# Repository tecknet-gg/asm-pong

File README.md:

<div align="center">

  <h1>asm-pong</h1>

  <p>pong implemented in assembly!</p>

</div>

## What!?

Basically what the subheading said! The classic game of pong implemented in assembly, running on a PIC16F18346 based console(-ish).

The PIC16F18346 console boasts a whopping 2KB of RAM, and a massive 28KB of flash memory, clocked at a blazing 32MHz! The game is displayed on a 128x64px OLED screen, with the player paddles being controlled by two potentiometers. Scores are displayed on two dedicated seven segment displays, with the sound effects being generated by a singular active buzzer. The console uses 3.3V, supplied by a regulated (up to 6V) power supply. Also features a dedicated ICSP header for easy programming using a PICkit3 or similar. 

## Hardware Overview
- PIC16F18346: Enhanced 8 bit, 20 pin mid-range PIC
- SSD1306: 128x64 pixel SPI OLED screen
- Alps RK09: Input potentiometers
- MCP1700-3302E: 3.3V regulated input
- 74HC595N: Daisy chained shift registers
- LD3161-AS: 0.36" red seven segment displays

## BOM

The detailed bill of materials file can be found under [pcb/production/bom.csv](pcb/production/bom.csv). All the components were sourced from AliExpress besides the PIC, since LCSC has much better pricing for the same. The table is reproduced below for convenience.

>[!Note]
> The capacitor and resistor pricing is the entire bundle price, including all the required values for this project.

| Item                       | Quantity | Description              |  Price | Source                                                                                                                                                                                                  |
| -------------------------- | -------: | ------------------------ | -----: | ------------------------------------------------------------------------------------------------------------------------------------------------------------------------------------------------------- |
| PIC16F18346-I/P            |        1 | Microcontroller          |  £1.81 | [LCSC](https://www.lcsc.com/product-detail/C647086.html?s_z=n_q_pic16f18346&spm=wm.fly.bg.0.xh&lcsc_vid=RFZZAwJQR1YIUFFXEgMNVgdQQAUIAQEER1IKUlZfRlcxVlNeQFhfXlBeRFFcVTsOAxUeFF5JWBYZEEoKFBINSQcJGk4%3D) |
| 100nF Ceramic Capacitor    |        7 | Decoupling capacitor     |      £1.93 | [AliExpress](https://www.aliexpress.com/item/1005008244407175.html?spm=a2g0o.order_list.order_list_main.203.33291802JVuyPM)                                                                             |
| 1µF Electrolytic Capacitor |        2 | Bulk capacitor           |      £1.96 | [AliExpress](https://www.aliexpress.com/item/1005006244064108.html?spm=a2g0o.order_list.order_list_main.316.33291802JVuyPM)                                                                             |
| SSD1306                    |        1 | OLED screen              |  £2.33 | [AliExpress](https://www.aliexpress.com/item/1005006379964006.html?spm=a2g0o.order_list.order_list_main.180.33291802JVuyPM)                                                                             |
| SN74HC595                  |        2 | Shift registers          |  £0.80 | [AliExpress](https://www.aliexpress.com/item/32796581727.html?spm=a2g0o.order_list.order_list_main.163.33291802JVuyPM)                                                                                  |
| LD-3161-AS                 |        2 | Seven-segment display    |  £2.33 | [AliExpress](https://www.aliexpress.com/item/1005007531476613.html?spm=a2g0o.order_list.order_list_main.158.33291802JVuyPM)                                                                             |
| Tactile Buttons            |        2 | Push buttons             |  £1.16 | [AliExpress](https://www.aliexpress.com/item/1005010485096642.html?spm=a2g0o.order_list.order_list_main.138.33291802JVuyPM)                                                                             |
| RV09 Potentiometers        |        2 | Potentiometers           |  £1.08 | [AliExpress](https://www.aliexpress.com/item/4000665266312.html?spm=a2g0o.order_list.order_list_main.128.33291802JVuyPM)                                                                                |
| Buzzer                     |        1 | Active buzzer            |  £1.80 | [AliExpress](https://www.aliexpress.com/item/1005010321957502.html?spm=a2g0o.order_list.order_list_main.80.33291802JVuyPM)                                                                              |
| 2N2222 NPN                 |        1 | Buzzer transistor        |  £1.00 | [AliExpress](https://www.aliexpress.com/item/1005005776372882.html?spm=a2g0o.order_list.order_list_main.68.33291802JVuyPM)                                                                              |
| 1N4148 Diode               |        1 | Flyback diode            |  £1.00 | [AliExpress](https://www.aliexpress.com/item/1005008512103805.html?spm=a2g0o.order_list.order_list_main.50.33291802JVuyPM)                                                                              |
| Knurled Metal Tone Knob    |        2 | Potentiometer knob       |  £2.01 | [AliExpress](https://www.aliexpress.com/item/1005002748625431.html?spm=a2g0o.order_list.order_list_main.35.33291802JVuyPM)                                                                              |
| MCP1700-3302E/TO           |        1 | 3.3V LDO                 |  £2.39 | [AliExpress](https://www.aliexpress.com/item/1005012279859529.html?spm=a2g0o.order_list.order_list_main.17.33291802JVuyPM)                                                                              |
| DC Power Barrel            |        1 | VIN input                |  £1.00 | [AliExpress](https://www.aliexpress.com/item/1005003329078538.html)                                                                                                                                     |
| 220Ω THT Resistor          |       16 | Current limiting         | £2.69|[AliExpress](https://www.aliexpress.com/item/1005007714306585.html?spm=a2g0o.order_list.order_list_main.98.74b31802kVDw05)                                                                                                                                                                                                       |
| 10kΩ THT Resistor          |        3 | RC/MCLR pull-up          |      £2.69|[AliExpress](https://www.aliexpress.com/item/1005007714306585.html?spm=a2g0o.order_list.order_list_main.98.74b31802kVDw05)                                                                                                                                                                                                     |
| 1kΩ THT Resistor           |        1 | Transistor base resistor |    £2.69  | [AliExpress](https://www.aliexpress.com/item/1005007714306585.html?spm=a2g0o.order_list.order_list_main.98.74b31802kVDw05)                                                                                                                                                                                                       |
| PICkit 3                   |        1 | ICSP programmer          | £14.19 | [AliExpress](https://www.aliexpress.com/item/1005007470418989.html?spm=a2g0o.order_list.order_list_main.168.33291802JVuyPM)                                                                             |
| PCB                        |        5 | Custom PCB               |     ~   | [pcb/production](pcb/production)                                                                           |

## Schematic

## PCB

## Assembly

PCB production files can be found under [pcb/production](pcb/production). Board is under 100x100mm, so should cost less than $5 for five boards from either [PCBWay](https://www.pcbway.com/) or [JLCPCB](https://www.jlcpcb.com/). I personally sourced them from JLC. All components are THT, so they should be very easy to solder. Follow the component references as given by the [schematic pdf](assets/schematic.pdf). Its a straightforward assembly, there isn't much else to say!

The case can be found in the [case](case/) directory. The taper angle is 15º, so I would recommend printing the model angled at 15º such that the top face is parallel to the bed, with ironing turned on for the best finish. PLA is the recommended material. 

With the case printed, the PCB mounts using the M2 mounting holes. No extra hardware needed, it just slots into the case. The case also has small indents in the bottom for rubbery grips. Just fill the indents with hot-glue, then overfill the indent very slightly to make a rubber grip. 

## Modifying source code

If you would like to make your own changes to the source code, you'll obviously have to recompile to get the new .hex! To get you started on that, here are a few recommendations.

First, I would lean towards using VSCode over MPLABX IDE. VSCode does require a fair bit more setup, over MPLABX, which is just plug and play, but in my opinion, the overall developer experience is worth that effort, since you get access to all of VSCode's quality of life features.

If you end up using VSCode, you'll need to install the MPLAB extension pack. Using the MCC that comes installed with this pack, you can configure your config bits and such. With that, you then set the compiler to PIC Assembly (PIC-AS/XC8). I would also then recommend you make a custom build task in ```.vscode/task.json```, similar to this:

```json
{
    "version": "2.0.0",
    "tasks": [
        {
            "label": "Build PIC HEX",
            "type": "shell",
            "command": "cmake --build _build/asm-pong/default && cp $(find out -name '*.hex' | head -n 1) out/output.hex",
            "group": {
                "kind": "build",
                "isDefault": true
            },
            "problemMatcher": [],
            "presentation": {
                "echo": true,
                "reveal": "always",
                "focus": false,
                "panel": "shared",
                "showReuseMessage": false,
                "clear": false
            }
        }
    ]
}
```

Hitting the build shortcut will then produce the ```output.hex``` that you can then flash. 

If you choose to go down the MPLABX IDE, all the build tasks and such should work natively without any setup. You also have easier access to the simulators and such. 

## Flashing firmware

To flash the firmware to the PIC, you need to use the ICSP header. The easiest way to flash the firmware is with a PICkit3 or above, and the [MPLAB IPE Software](https://www.microchip.com/en-us/tools-resources/develop/mplab-x-ide) (you may have to install the PIC16F1xxxx pack manually).
> [!NOTE]
> MPLAB IPE support for legacy PICkits (2 and 3) was dropped after v6.20. These PICkits are cheaper to purchase, and work just fine for this use case. To use with MPLAB IPE, install v6.20 or prior. My PIC was flashed with a PICkit3 using MPLAB IPE v6.00. Alternatively, you can use a terminal utility like ```ipecmd```, ```pkcmd-lx``` or similar. 

> [!NOTE]
> You can also flash the PIC by bit banging the ICSP protocol on another microcontroller. You do not need a level shifting circuit since Low Voltage Programming should be supported by the PIC16F18346. This has NOT been verified.

Assuming you're using a PICkit with MPLAB IPE, select the PIC16F18346 under devices, and your tool in the tool selection menu. If the software isn't detecting your PICkit, unplug it, hold down the button, then plug it back in, keeping the button pressed for a few more seconds. Then double check if is being detected as connected to a port on your system information panel. Once you have it connected, enable the advanced mode (under Settings > Advanced Mode). With this enabled, you should see various settings appear on the sidebar. Go to the power setting, and tick the box saying "Power target circuit from PIC". Ensure the PIC16F18346 (and the console by extension), is powered by 3.3V before proceeding.

>[!NOTE]
> If you can't see the PIC under the device options, you probably don't have the pack installed and linked. [Download](https://packs.download.microchip.com/Microchip.PIC16F1xxxx_DFP.1.31.465.atpack) the pack here. Locate the ```.mchp_packs``` directory, and drop the file in there. 

>[!WARNING]
> If you fail to check "Power target circuit from PIC", you may damage either the PICkit, or the PIC itself. Double check this setting is enabled, and read the output logs as the PICkit connects to the PIC. 

With all that setup, plug in the PICkit's headers into the ICSP header on the board. The top pin of the header (pin closest to the screen) is MCLR. Match that with the pinout of your PICkit. Now download and load the [.hex](out/output.hex) file into the IPE, and click program. Et voila, you should have a fully programmed PIC!

>[!NOTE]
> If you see glitchy behaviour, or the screen not starting up, make sure the PCB is disconnected from the programmer. When the headers are still connected, it behaves oddly. After that, hit the reset button to re-boot the PIC. 

## Demo

A demo video of an entire game being played out can be found on my [YouTube channel](https://www.youtube.com/watch?v=OH-_ZXIoXKA). Here is a picture of the completed build!

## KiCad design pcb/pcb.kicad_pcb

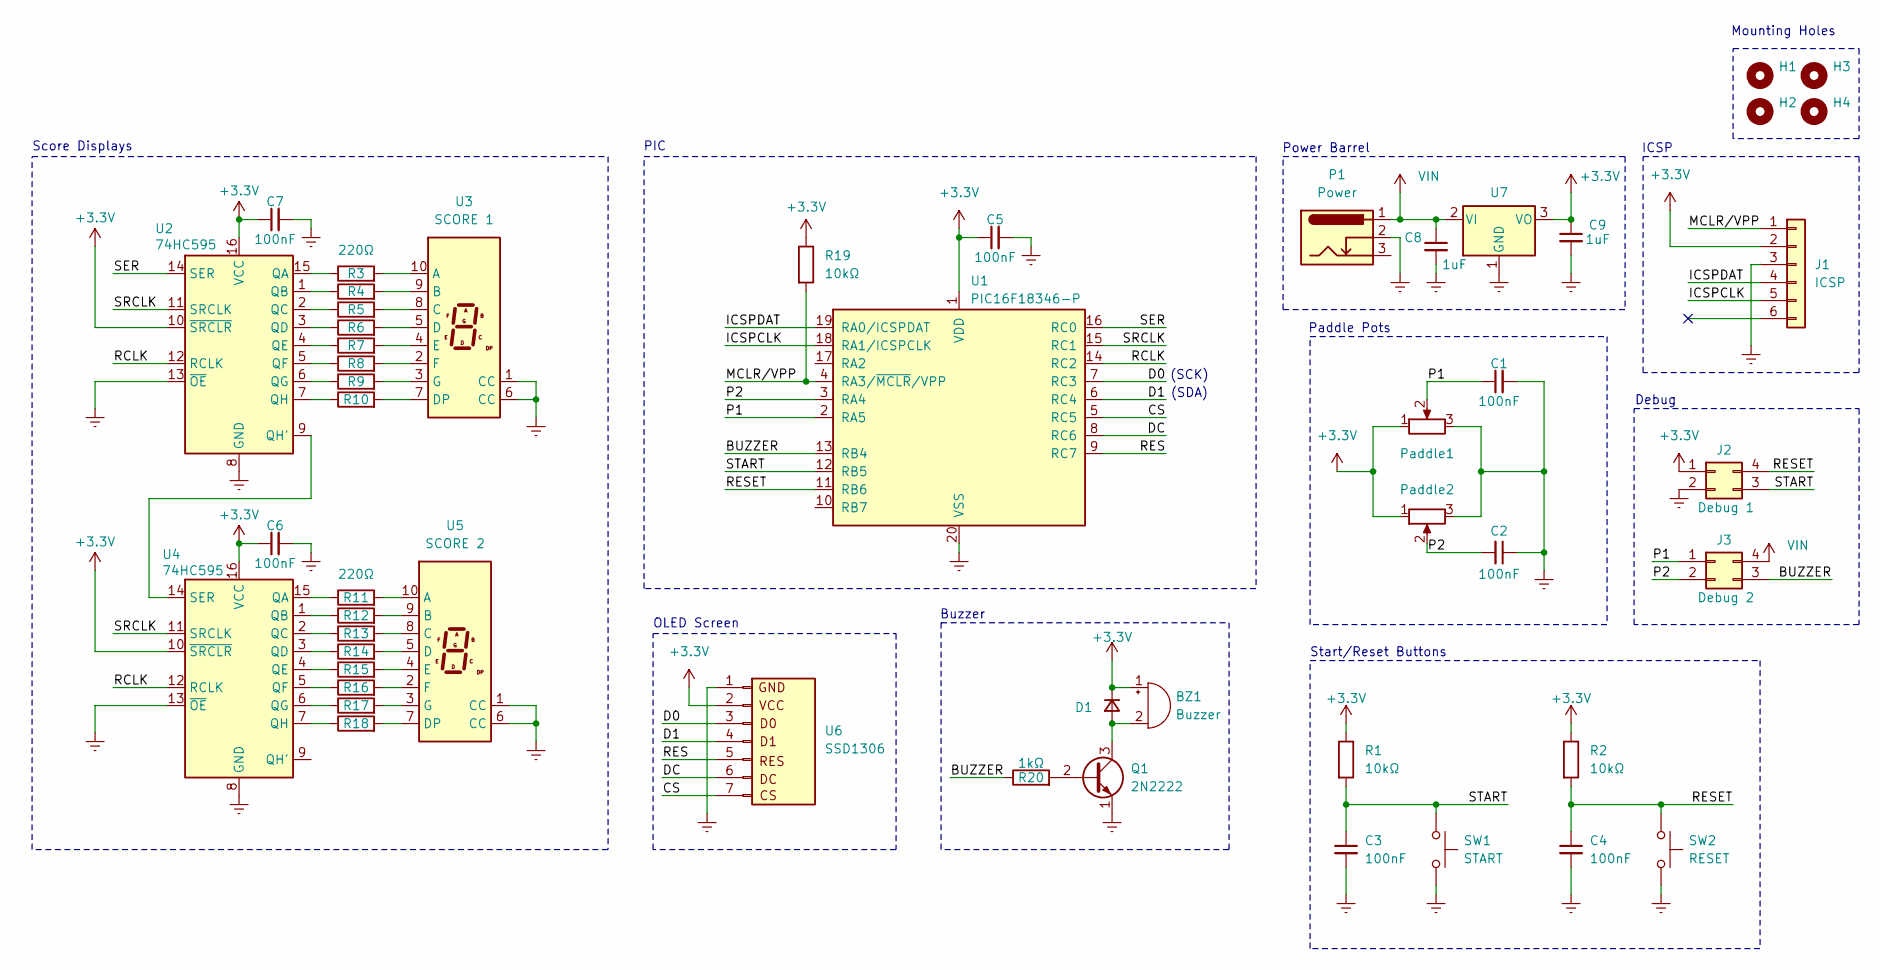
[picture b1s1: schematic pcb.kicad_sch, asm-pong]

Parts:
BZ1: Buzzer; Buzzer_12x9.5RM7.6
C1, C2, C3, C4, C5, C6, C7: 100nF; C_Disc_D5.0mm_W2.5mm_P5.00mm
C8, C9: 1uF; C_Radial_D4.0mm_H7.0mm_P1.50mm
D1: D_Small; D_DO-35_SOD27_P7.62mm_Horizontal
H1, H2, H3, H4: MountingHole; MountingHole_2.2mm_M2
J1: ICSP; PinHeader_1x06_P2.54mm_Vertical
J2: Debug 1; PinHeader_2x02_P2.54mm_Vertical
J3: Debug 2; PinHeader_2x02_P2.54mm_Vertical
P1: Power; BarrelJack_Horizontal
Paddle1, Paddle2: R_Potentiometer; Potentiometer_Alps_RK09K_Single_Vertical
Q1: 2N2222; TO-92_Inline_Wide
R1, R2, R19: 10kΩ; R_Axial_DIN0207_L6.3mm_D2.5mm_P10.16mm_Horizontal
R3, R11: 220Ω; R_Axial_DIN0207_L6.3mm_D2.5mm_P10.16mm_Horizontal
R4, R6, R8, R10, R12, R14, R16, R18: 330; R_Axial_DIN0207_L6.3mm_D2.5mm_P10.16mm_Horizontal
R5, R7, R9, R13, R15, R17: 330Ω; R_Axial_DIN0207_L6.3mm_D2.5mm_P10.16mm_Horizontal
R20: 1kΩ; R_Axial_DIN0207_L6.3mm_D2.5mm_P10.16mm_Horizontal
SW1: START; SW_PUSH-12mm
SW2: RESET; SW_PUSH-12mm
U1: PIC16F18346-P; DIP-20_W7.62mm_Socket
U2, U4: 74HC595; DIP-16_W7.62mm_Socket_LongPads
U3: SCORE 1; 0.36in 3161AS
U5: SCORE 2; 0.36in 3161AS
U6: SSD1306; PinSocket_1x07_P2.54mm_Vertical
U7: MCP1700x-330xxTO; TO-92_Inline

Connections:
+3.3V: BZ1.1 (+), C5.1, C6.1, C7.1, C9.1, D1.1 (K), J1.2, J2.1, Paddle1.1, Paddle2.1, R1.1, R2.1, R19.1, U1.1 (VDD), U2.10 (~SRCLR), U2.16 (VCC), U4.10 (~SRCLR), U4.16 (VCC), U6.2, U7.3 (VO)
/BUZZER: J3.3, R20.1, U1.13 (RB4)
/CS: U1.5 (RC5), U6.7
/D0: U1.7 (RC3), U6.3
/D1: U1.6 (RC4), U6.4
/DC: U1.8 (RC6), U6.6
/ICSPCLK: J1.5, U1.18 (RA1/ICSPCLK)
/ICSPDAT: J1.4, U1.19 (RA0/ICSPDAT)
/MCLR/VPP: J1.1, R19.2, U1.4 (RA3/~MCLR/VPP)
/P1: C1.1, J3.1, Paddle1.2, U1.2 (RA5)
/P2: C2.2, J3.2, Paddle2.2, U1.3 (RA4)
/RCLK: U1.14 (RC2), U2.12 (RCLK), U4.12 (RCLK)
/RES: U1.9 (RC7), U6.5
/RESET: C4.1, J2.4, R2.2, SW2.1, U1.11 (RB6)
/SER: U1.16 (RC0), U2.14 (SER)
/SRCLK: U1.15 (RC1), U2.11 (SRCLK), U4.11 (SRCLK)
/START: C3.1, J2.3, R1.2, SW1.1, U1.12 (RB5)
Earth: C1.2, C2.1, C3.2, C4.2, C5.2, C6.2, C7.2, C8.2, C9.2, J1.3, J2.2, P1.2, Paddle1.3, Paddle2.3, Q1.1 (E), SW1.2, SW2.2, U1.20 (VSS), U2.8 (GND), U2.13 (~OE), U3.1 (CC), U3.6 (CC), U4.8 (GND), U4.13 (~OE), U5.1 (CC), U5.6 (CC), U6.1, U7.1 (GND)
unnamed: BZ1.2 (-), D1.2 (A), Q1.3 (C)
unnamed: Q1.2 (B), R20.2
unnamed: R3.1, U2.15 (QA)
unnamed: R4.1, U2.1 (QB)
unnamed: R5.1, U2.2 (QC)
unnamed: R6.1, U2.3 (QD)
unnamed: R7.1, U2.4 (QE)
unnamed: R8.1, U2.5 (QF)
unnamed: R9.1, U2.6 (QG)
unnamed: U2.9 (QH'), U4.14 (SER)
unnamed: R10.1, U2.7 (QH)
unnamed: R3.2, U3.10 (A)
unnamed: R4.2, U3.9 (B)
unnamed: R5.2, U3.8 (C)
unnamed: R6.2, U3.5 (D)
unnamed: R10.2, U3.7 (DP)
unnamed: R7.2, U3.4 (E)
unnamed: R8.2, U3.2 (F)
unnamed: R9.2, U3.3 (G)
unnamed: R11.1, U4.15 (QA)
unnamed: R12.1, U4.1 (QB)
unnamed: R13.1, U4.2 (QC)
unnamed: R14.1, U4.3 (QD)
unnamed: R15.1, U4.4 (QE)
unnamed: R16.1, U4.5 (QF)
unnamed: R17.1, U4.6 (QG)
unnamed: R18.1, U4.7 (QH)
unnamed: R11.2, U5.10 (A)
unnamed: R12.2, U5.9 (B)
unnamed: R13.2, U5.8 (C)
unnamed: R14.2, U5.5 (D)
unnamed: R18.2, U5.7 (DP)
unnamed: R15.2, U5.4 (E)
unnamed: R16.2, U5.2 (F)
unnamed: R17.2, U5.3 (G)
VIN: C8.1, J3.4, P1.1, U7.2 (VI)

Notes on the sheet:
Mounting Holes
Start/Reset Buttons
Paddle Pots
(SCK)
(SDA)
PIC
Power Barrel
Debug
ICSP
OLED Screen
Score Displays
Buzzer

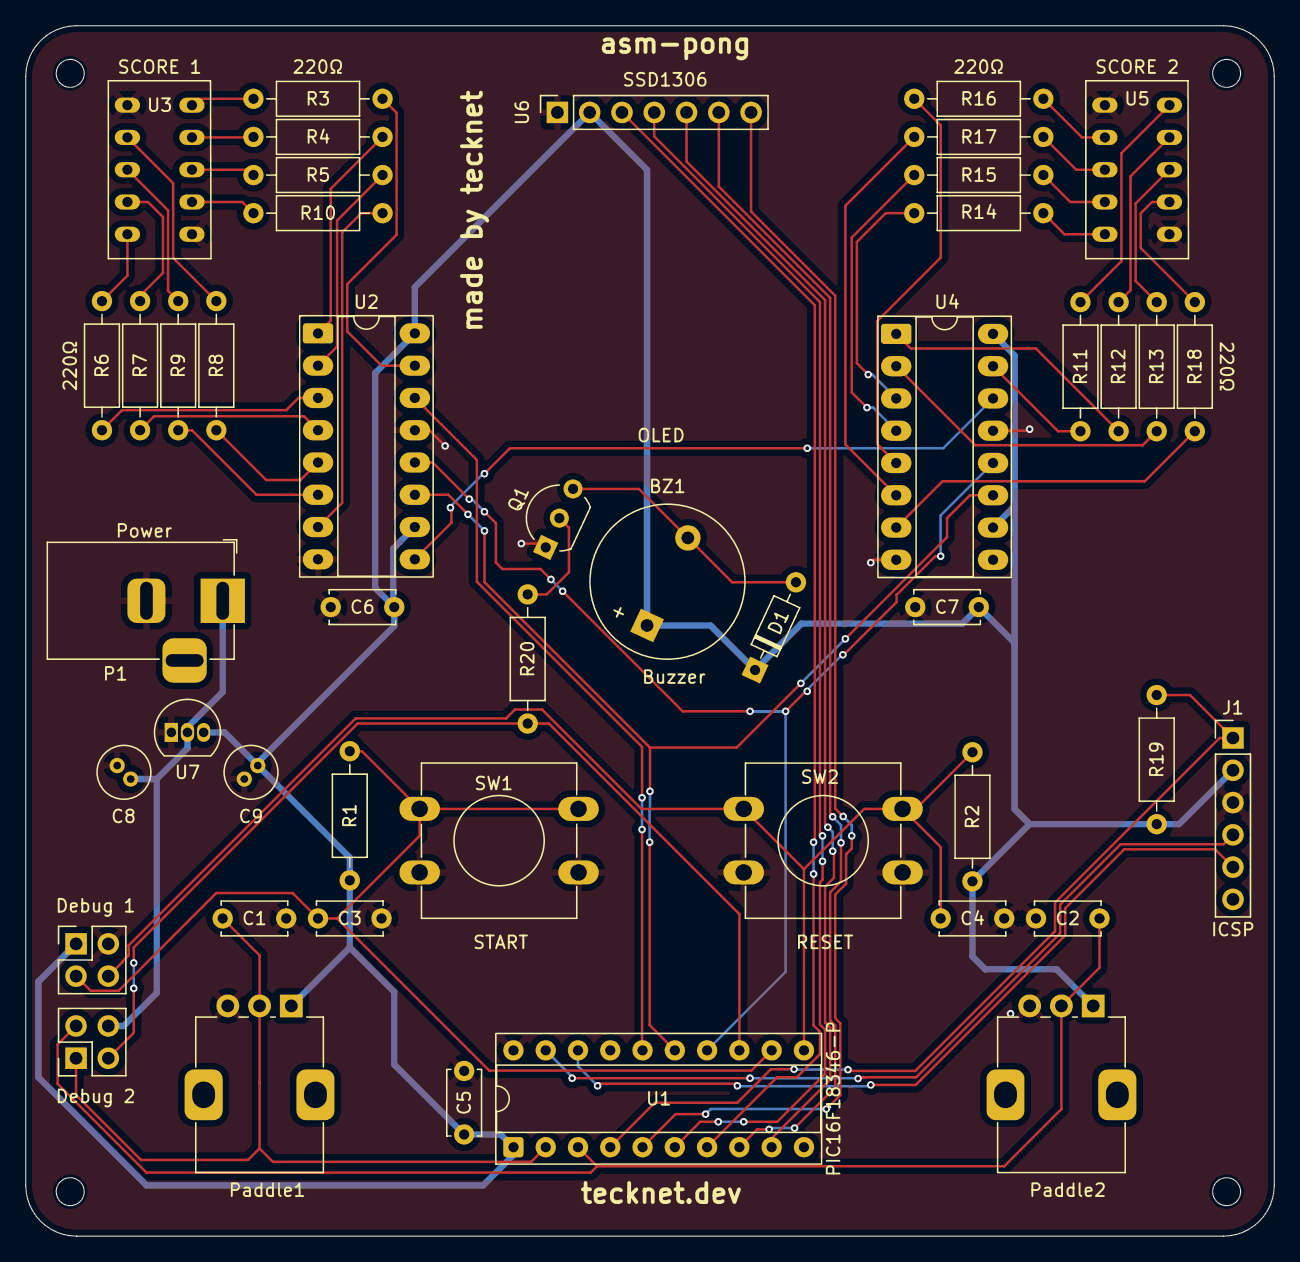
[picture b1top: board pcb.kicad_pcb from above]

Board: 2 copper layers, 98.2 x 95.2 mm, 51 parts (0 on the bottom side), 54 nets.
